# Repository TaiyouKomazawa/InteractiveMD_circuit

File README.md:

# InteractiveMD_circuit

## 概要

小出力DCモータ(12V MAX 5Aクラス)の汎用的な制御デバイス。
https://github.com/TaiyouKomazawa/InteractiveMD.git の回路図  

## 使用CAD

Autodesk Eagle

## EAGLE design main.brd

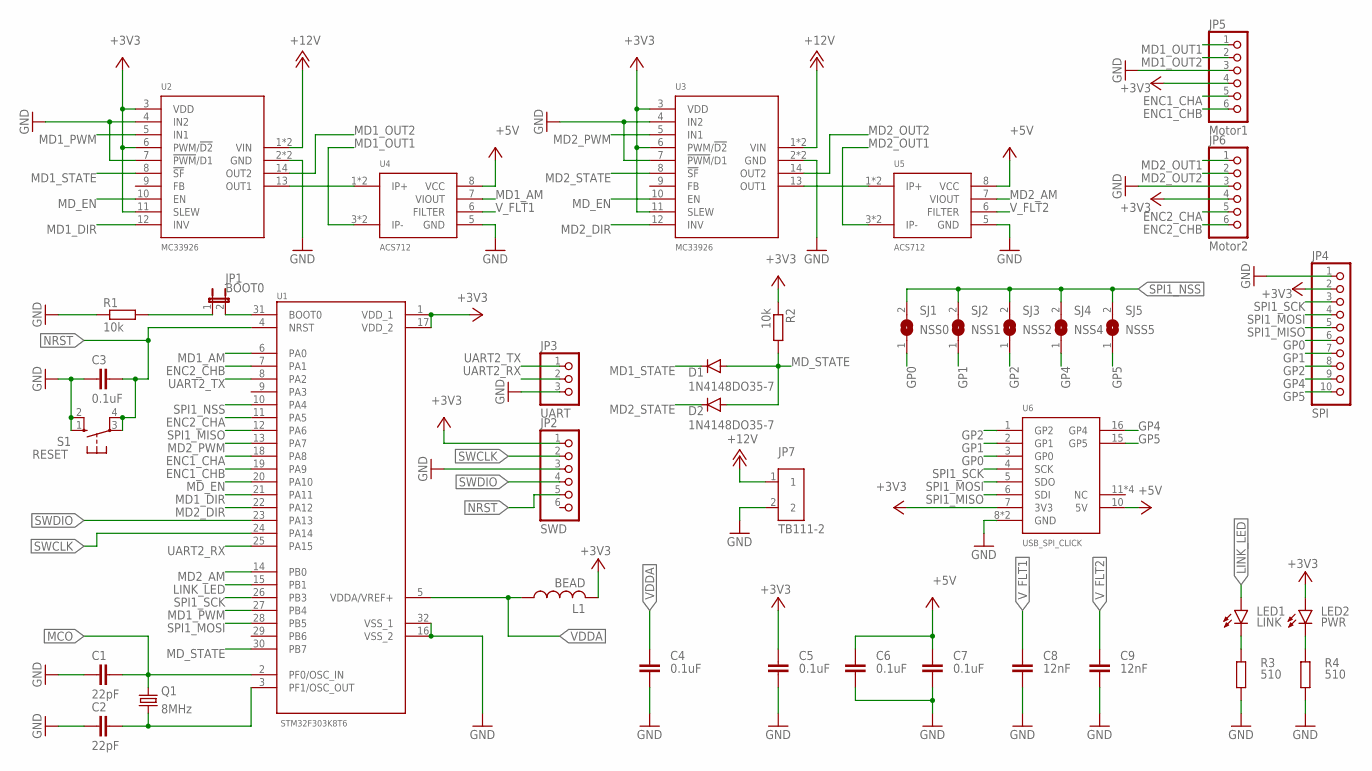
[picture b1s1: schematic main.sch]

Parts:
C1, C2: 22pF; C1608
C3, C4, C5, C6, C7: 0.1uF; C1608
C8, C9: 12nF; C1608
D1, D2: 1N4148DO35-7; DO35-7
JP1: BOOT0; JP1
JP2: SWD; 1X06
JP3: UART; 1X03
JP4: SPI; 1X10
JP5: Motor1; 1X06/90
JP6: Motor2; 1X06/90
JP7: TB111-2; TB111-2-2-U-1-1
L1: BEAD; L2012C
LED1: LINK; LED3MM
LED2: PWR; LED3MM
Q1: 8MHz; HC49/S
R1, R2: 10k; R1210
R3, R4: 510; R1210
S1: RESET; B3F-10XX
SJ1: NSS0; SJ
SJ2: NSS1; SJ
SJ3: NSS2; SJ
SJ4: NSS4; SJ
SJ5: NSS5; SJ
U1: STM32F303K8T6; QFP80P900X900X160-32N
U2, U3: MC33926; SINGLE
U4, U5: ACS712; SOIC8
U6: USB_SPI_CLICK; MIKROBUS

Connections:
+3V3: C5.1, JP2.1, JP4.2, JP5.4, JP6.4, L1.2, LED2.A, R2.1, U1.1 (VDD_1), U1.17 (VDD_2), U2.3 (VDD), U2.6 (PWM/!D2!), U2.11 (SLEW), U3.3 (VDD), U3.6 (PWM/!D2!), U3.11 (SLEW), U6.7 (3V3)
+5V: C6.1, C7.1, U4.8 (VCC), U5.8 (VCC), U6.10 (5V)
+12V: JP7.1, U2.1 (VIN), U2.16 (VIN), U3.1 (VIN), U3.16 (VIN)
ENC1_CHA: JP5.5, U1.18 (PA8)
ENC1_CHB: JP5.6, U1.19 (PA9)
ENC2_CHA: JP6.5, U1.11 (PA5)
ENC2_CHB: JP6.6, U1.7 (PA1)
GND: C1.2, C2.2, C3.1, C4.2, C5.2, C6.2, C7.2, C8.2, C9.2, JP2.3, JP3.3, JP4.1, JP5.3, JP6.3, JP7.2, R1.1, R3.2, R4.2, S1.1 (S), S1.2 (S1), U1.16 (VSS_2), U1.32 (VSS_1), U2.2 (GND), U2.4 (IN2), U2.7 (!PWM!/D1), U2.15 (GND), U3.2 (GND), U3.4 (IN2), U3.7 (!PWM!/D1), U3.15 (GND), U4.5 (GND), U5.5 (GND), U6.8 (GND), U6.9 (GND)
GP0: JP4.6, SJ1.1, U6.3 (GP0)
GP1: JP4.7, SJ2.1, U6.2 (GP1)
GP2: JP4.8, SJ3.1, U6.1 (GP2)
GP4: JP4.9, SJ4.1, U6.16 (GP4)
GP5: JP4.10, SJ5.1, U6.15 (GP5)
LINK_LED: LED1.A, U1.15 (PB1)
MCO: C1.1, Q1.2, U1.2 (PF0/OSC_IN)
MD1_AM: U1.6 (PA0), U4.7 (VIOUT)
MD1_DIR: U1.21 (PA11), U2.12 (INV)
MD1_OUT1: JP5.1, U4.3 (IP-), U4.4 (IP-)
MD1_OUT2: JP5.2, U2.14 (OUT2)
MD1_PWM: U1.27 (PB4), U2.5 (IN1)
MD1_STATE: D1.C, U2.8 (!SF!)
MD2_AM: U1.14 (PB0), U5.7 (VIOUT)
MD2_DIR: U1.22 (PA12), U3.12 (INV)
MD2_OUT1: JP6.1, U5.3 (IP-), U5.4 (IP-)
MD2_OUT2: JP6.2, U3.14 (OUT2)
MD2_PWM: U1.13 (PA7), U3.5 (IN1)
MD2_STATE: D2.C, U3.8 (!SF!)
MD_EN: U1.20 (PA10), U2.10 (EN), U3.10 (EN)
MD_STATE: D1.A, D2.A, R2.2, U1.30 (PB7)
unnamed: JP1.2, U1.31 (BOOT0)
unnamed: C2.1, Q1.1, U1.3 (PF1/OSC_OUT)
unnamed: JP1.1, R1.2
unnamed: U2.13 (OUT1), U4.1 (IP+), U4.2 (IP+)
unnamed: U3.13 (OUT1), U5.1 (IP+), U5.2 (IP+)
unnamed: LED1.K (C), R3.1
unnamed: LED2.K (C), R4.1
NRST: C3.2, JP2.5, S1.3, S1.4 (P1), U1.4 (NRST)
SPI1_MISO: JP4.5, U1.12 (PA6), U6.6 (SDI)
SPI1_MOSI: JP4.4, U1.28 (PB5), U6.5 (SDO)
SPI1_NSS: SJ1.2, SJ2.2, SJ3.2, SJ4.2, SJ5.2, U1.10 (PA4)
SPI1_SCK: JP4.3, U1.26 (PB3), U6.4 (SCK)
SWCLK: JP2.2, U1.24 (PA14)
SWDIO: JP2.4, U1.23 (PA13)
UART2_RX: JP3.2, U1.25 (PA15)
UART2_TX: JP3.1, U1.8 (PA2)
VDDA: C4.1, L1.1, U1.5 (VDDA/VREF+)
V_FLT1: C8.1, U4.6 (FILTER)
V_FLT2: C9.1, U5.6 (FILTER)

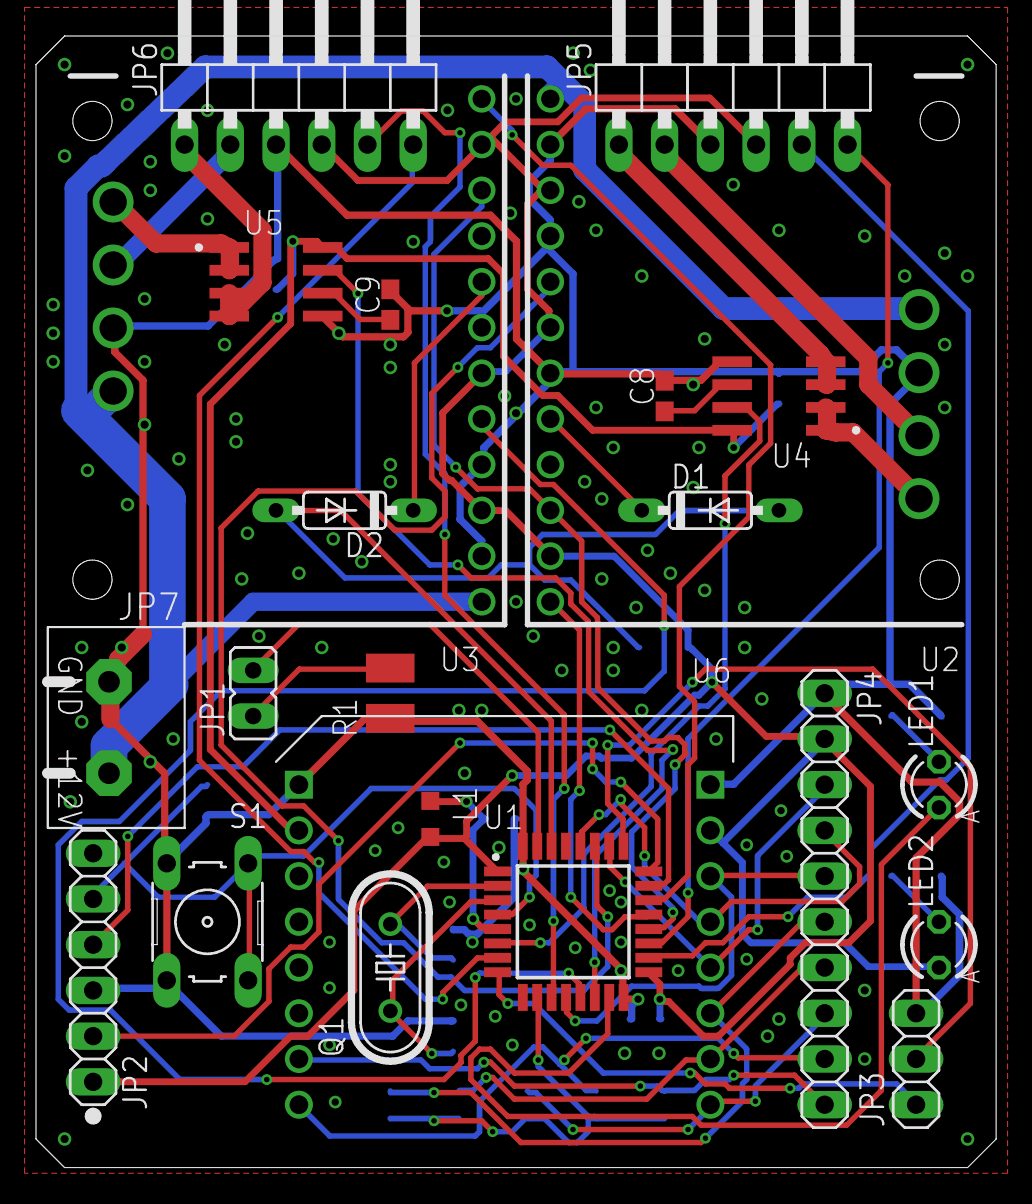
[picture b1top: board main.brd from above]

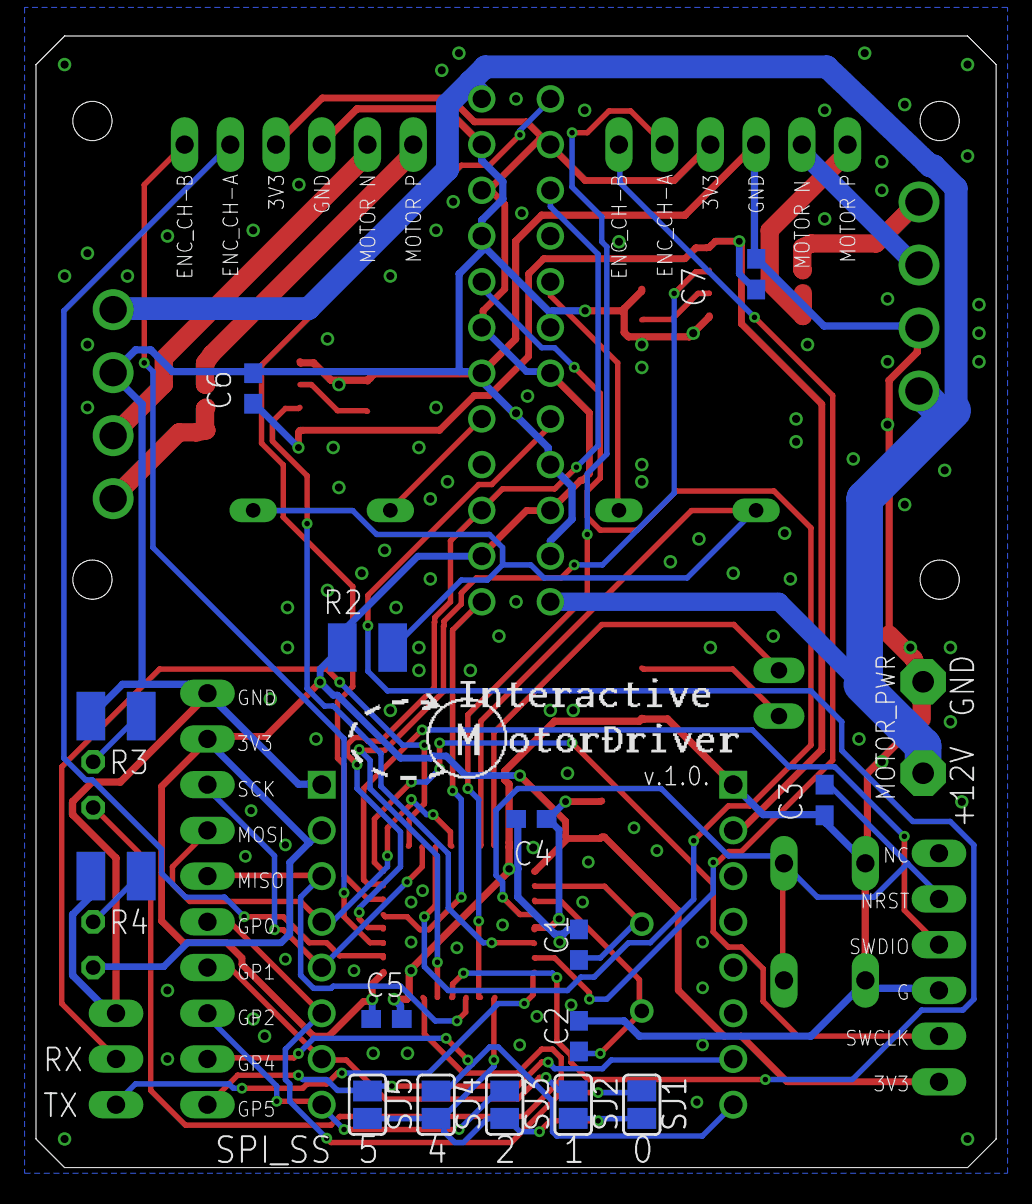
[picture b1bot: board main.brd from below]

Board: 2 copper layers, 53.3 x 62.9 mm, 39 parts (16 on the bottom side), 48 nets.

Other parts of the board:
U$1: LOGO_A_X3

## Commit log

2022-01-22 [New] IMDの回路図を追加
2022-01-22 [Doc] READMEを追加
